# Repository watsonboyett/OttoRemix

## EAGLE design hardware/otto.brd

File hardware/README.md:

# Hardware

## Overview

Control board for servos, displays, and sensors.

## Features

### MCU
* Raytac MDBT50 module, using Nordic nRF52840 MCU
* Custom board design (very similar to Adafruit Feather nRF52840 express)

### Power
* LiPo battery input (using JST-PH header)
* Boost converter for battery to get 5V supply
* USB-C charging (rate is configurabale, default is set to 200mA)
* Power/shut-down switch, battery can be charged while ON or OFF

### Servo Motors
* 6 servo motor connections (3 on left side, 3 on right side)
* Powered from 5V supply

### LED Matrix
* P/N: Adafruit Featherwing LED Matrix
* Uses I2C bus for communication (address: 0x70)
* Powered from 5V supply
* 4-pin header

### Touch Sensor 
* P/N: Azoteq TPS43-201A-S
* Uses I2C bus for communication (address: 0x74)
* Uses GPIO input for interrupt signal from sensor
* Powered from 3.3V supply
* 5-pin header

### IMU 
* P/N: Bosch BMX160
* Uses I2C bus for communication (address: 0x68)

### Ultrasonic Range Sensor
* P/N: 
* Uses 2 GPIO pins for trig and echo signals
* Powered from 3.3V supply
* 4-pin header

### Speaker
* P/N: 
* Uses PWM output from MCU to drive audio amplifier
* RC filter on amp inputs
* Powered from 5V supply
* 2-pin header

### Buzzer
* P/N: 
* Uses PWM output from MCU
* Uses transistor to drive buzzer from 5V supply
* 2-pin header

### ON/OFF Switch
* Controls the 3.3V and 5V regulator enable circuitry 
* Not wired in-line with power supplies, so low power switched can be used
* Very low current draw when in shut-down (approx. 40 uA)
* 2 pin header

## Manufacturing Info

* outer dimensions: 56 mm x 49 mm (2.2" x 1.9")
* thickness: 1.00 mm (0.040")
* min. trace/space: 8 mil, 8 mil
* min. drill: 0.25 mm (10 mil)
* min. cutout radius: 0.4 mm (0.015")
* surface finish: ENIG
* soldermask: both sides, black
* silkscreen: both sides, white
* impedance control: none
* stackup: 4 layers

## Revision History

### v1A

* Initial design

### v2A

* Fixed schematic typo: D8 changed to D9, to reflect actual pin number
* Added 100 uF caps near servo and LED power supply pins
* Changed external board caps to 10 uF
* Removed buzzer (uses speaker only)
* Moved external connectors/silkscreen to bottom side (re-arranged all locations)
* Added power selector IC (P/N: TPS2115) for USB-VBUS vs. battery (defaults to VBUS if both present)
* Added support/connector for PIR sensor (pwr, gnd, IO/interrupt)
* Added PDM microphone (P/N: SPK0641HT4H, port on top)
* Added temp/humidity sensor (P/N: SHT41)
* Added ambient light sensor (P/N: APDS-9250) and light pipe
* Added air pressure sensor (P/N: LPS22HB)
* Added air quality/VOC sensor (P/N: SGP41)
* Added neopixel LED (SK6812-mini) and light pipe

### Future Changes

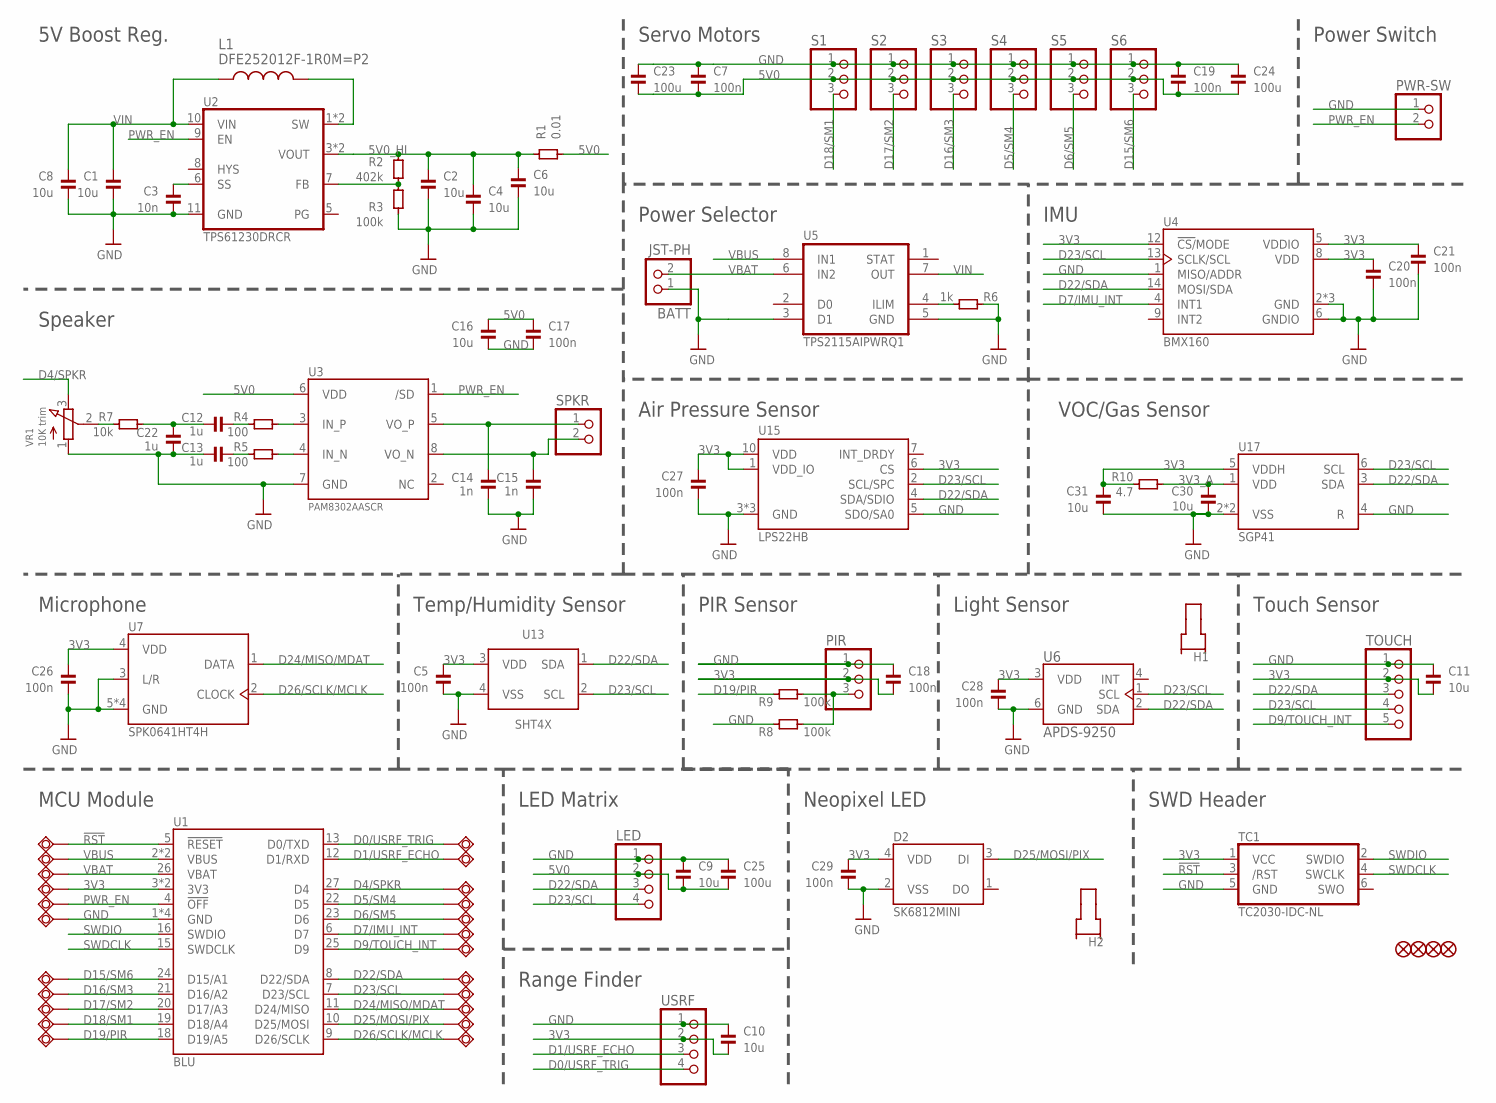
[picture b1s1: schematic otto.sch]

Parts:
3V3: TPSQTP10R; TP10R
BATT: JST-PH; JSTPH2-S2B
C1, C2, C4, C6, C8, C9, C10, C11, C16, C30, C31: 10u; _0603; MPN CL21A106KAYNNNE
C3: 10n; _0603; MPN CL21A106KAYNNNE
C5, C7, C17, C18, C19, C20, C21, C26, C27, C28, C29: 100n; _0603; MPN CL21A106KAYNNNE
C12, C13, C22: 1u; _0603; MPN CL21A106KAYNNNE
C14, C15: 1n; _0603; MPN CL21A106KAYNNNE
C23, C24, C25: 100u; _1206; MPN CL21A106KAYNNNE
D0, D1, D4, D5, D6, D7, D9, D15, D16, D17, D18, D19, D24, D25, D26: TPSQTP10R; TP10R
D2: SK6812MINI
FID1, FID2, FID3, FID5: FIDUCIAL0.8MM; FIDUCIAL_0.8MM
GND: TPSQTP10R; TP10R
H1, H2: VLP-XXX-X
L1: DFE252012F-1R0M=P2; INDC2520X120N
LED: PINHD-1X4; 1X04
PEN: TPSQTP10R; TP10R
PIR: PINHD-1X3; 1X03
PWR-SW: PINHD-1X2; 1X02
R1: 0.01; _0603
R2: 402k; _0603
R3, R8, R9: 100k; _0603
R4, R5: 100; _0603
R6: 1k; _0603
R7: 10k; _0603
R10: 4.7; _0603
RST: TPSQTP10R; TP10R
S1, S2, S3, S4, S5, S6: PINHD-1X3; 1X03
SCL: TPSQTP10R; TP10R
SDA: TPSQTP10R; TP10R
SPKR: PINHD-1X2; 1X02
TC1: TC2030-IDC-NL; TC2030-NL
TOUCH: PINHD-1X5; 1X05
U1: BLU
U2: TPS61230DRCR; VREG_V62/16624-01YE
U3: PAM8302AASCR; MSOP8_0.65MM
U4: BMX160; PQFN50P250X300X100-14N
U5: TPS2115AIPWRQ1; SOP65P640X120-8N
U6: APDS-9250; SON65P200X200X75-6N
U7: SPK0641HT4H; SPK0641HT4H-1
U13: SHT4X; SHT4X-DFN4
U15: LPS22HB; HLGA-10L
U17: SGP41
USRF: PINHD-1X4; 1X04
VBS: TPSQTP10R; TP10R
VBT: TPSQTP10R; TP10R
VR1: 10K trim; TRIMPOT_BOURNS_3303W

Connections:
3V3: 3V3.TP, C5.1, C10.2, C11.2, C18.2, C20.1, C21.1, C26.1, C27.1, C28.1, C29.1, C31.1, D2.4 (VDD), PIR.2, R10.1, TC1.1 (VCC), TOUCH.2, U1.3 (3V3), U1.28 (3V3), U4.5 (VDDIO), U4.8 (VDD), U4.12 (!CS/!MODE), U6.3 (VDD), U7.4 (VDD), U13.3 (VDD), U15.1 (VDD_IO), U15.6 (CS), U15.10 (VDD), U17.5 (VDDH), USRF.2
3V3_A: C30.1, R10.2, U17.1 (VDD)
5V0: C7.2, C9.2, C16.1, C17.1, C19.2, C23.2, C24.2, C25.2, LED.2, R1.1, S1.2, S2.2, S3.2, S4.2, S5.2, S6.2, U3.6 (VDD)
5V0_HI: C2.1, C4.1, C6.1, R1.2, R2.1, U2.3 (VOUT), U2.4 (VOUT)
!RST: RST.TP, TC1.3 (/RST), U1.5 (!RESET)
D0/USRF_TRIG: D0.TP, U1.13 (D0/TXD), USRF.4
D1/USRF_ECHO: D1.TP, U1.12 (D1/RXD), USRF.3
D4/SPKR: D4.TP, U1.27 (D4), VR1.3 (E)
D5/SM4: D5.TP, S4.3, U1.22 (D5)
D6/SM5: D6.TP, S5.3, U1.23 (D6)
D7/IMU_INT: D7.TP, U1.6 (D7), U4.4 (INT1)
D9/TOUCH_INT: D9.TP, TOUCH.5, U1.25 (D9)
D15/SM6: D15.TP, S6.3, U1.24 (D15/A1)
D16/SM3: D16.TP, S3.3, U1.21 (D16/A2)
D17/SM2: D17.TP, S2.3, U1.20 (D17/A3)
D18/SM1: D18.TP, S1.3, U1.19 (D18/A4)
D19/PIR: D19.TP, R9.1, U1.18 (D19/A5)
D22/SDA: LED.3, SDA.TP, TOUCH.3, U1.8 (D22/SDA), U4.14 (MOSI/SDA), U6.2 (SDA), U13.1 (SDA), U15.4 (SDA/SDIO), U17.3 (SDA)
D23/SCL: LED.4, SCL.TP, TOUCH.4, U1.7 (D23/SCL), U4.13 (SCLK/SCL), U6.1 (SCL), U13.2 (SCL), U15.2 (SCL/SPC), U17.6 (SCL)
D24/MISO/MDAT: D24.TP, U1.11 (D24/MISO), U7.1 (DATA)
D25/MOSI/PIX: D2.3 (DI), D25.TP, U1.10 (D25/MOSI)
D26/SCLK/MCLK: D26.TP, U1.9 (D26/SCLK), U7.2 (CLOCK)
GND: BATT.1, C1.2, C2.2, C3.2, C4.2, C5.2, C6.2, C7.1, C8.2, C9.1, C10.1, C11.1, C13.1, C14.1, C15.1, C16.2, C17.2, C18.1, C19.1, C20.2, C21.2, C22.1, C23.1, C24.1, C25.1, C26.2, C27.2, C28.2, C29.2, C30.2, C31.2, D2.2 (VSS), GND.TP, LED.1, PIR.1, PWR-SW.1, R3.2, R6.1, R8.1, S1.1, S2.1, S3.1, S4.1, S5.1, S6.1, TC1.5 (GND), TOUCH.1, U1.1 (GND), U1.14 (GND), U1.17 (GND), U1.30 (GND), U2.11 (GND), U3.7 (GND), U4.1 (MISO/ADDR), U4.2 (GND), U4.3 (GND), U4.6 (GNDIO), U4.7 (GND), U5.3 (D1), U5.5 (GND), U6.6 (GND), U7.3 (L/R), U7.5 (GND), U7.6 (GND), U7.7 (GND), U7.8 (GND), U13.4 (VSS), U15.3 (GND), U15.5 (SDO/SA0), U15.8 (GND), U15.9 (GND), U17.2 (VSS), U17.4 (R), U17.EP (VSS), USRF.1, VR1.1 (A)
unnamed: C3.1, U2.6 (SS)
unnamed: R2.2, R3.1, U2.7 (FB)
unnamed: R7.1, VR1.2 (S)
unnamed: C12.1, C22.2, R7.2
unnamed: PIR.3, R8.2, R9.2
unnamed: R6.2, U5.4 (ILIM)
unnamed: L1.2, U2.1 (SW), U2.2 (SW)
unnamed: C12.2, R4.1
unnamed: C13.2, R5.1
unnamed: R4.2, U3.3 (IN_P)
unnamed: R5.2, U3.4 (IN_N)
unnamed: C14.2, SPKR.1, U3.5 (VO_P)
unnamed: C15.2, SPKR.2, U3.8 (VO_N)
PWR_EN: PEN.TP, PWR-SW.2, U1.4 (!OFF), U2.9 (EN), U3.1 (/SD)
SWDCLK: TC1.4 (SWCLK), U1.15 (SWDCLK)
SWDIO: TC1.2 (SWDIO), U1.16 (SWDIO)
VBAT: BATT.2, U1.26 (VBAT), U5.6 (IN2), VBT.TP
VBUS: U1.2 (VBUS), U1.29 (VBUS), U5.8 (IN1), VBS.TP
VIN: C1.1, C8.1, L1.1, U2.10 (VIN), U5.7 (OUT)

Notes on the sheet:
MCU Module
5V Boost Reg.
SWD Header
Servo Motors
Power Switch
Touch Sensor
Range Finder
LED Matrix
Speaker
Microphone
IMU
Power Selector
Temp/Humidity Sensor
PIR Sensor
Light Sensor
Air Pressure Sensor
Neopixel LED
VOC/Gas Sensor

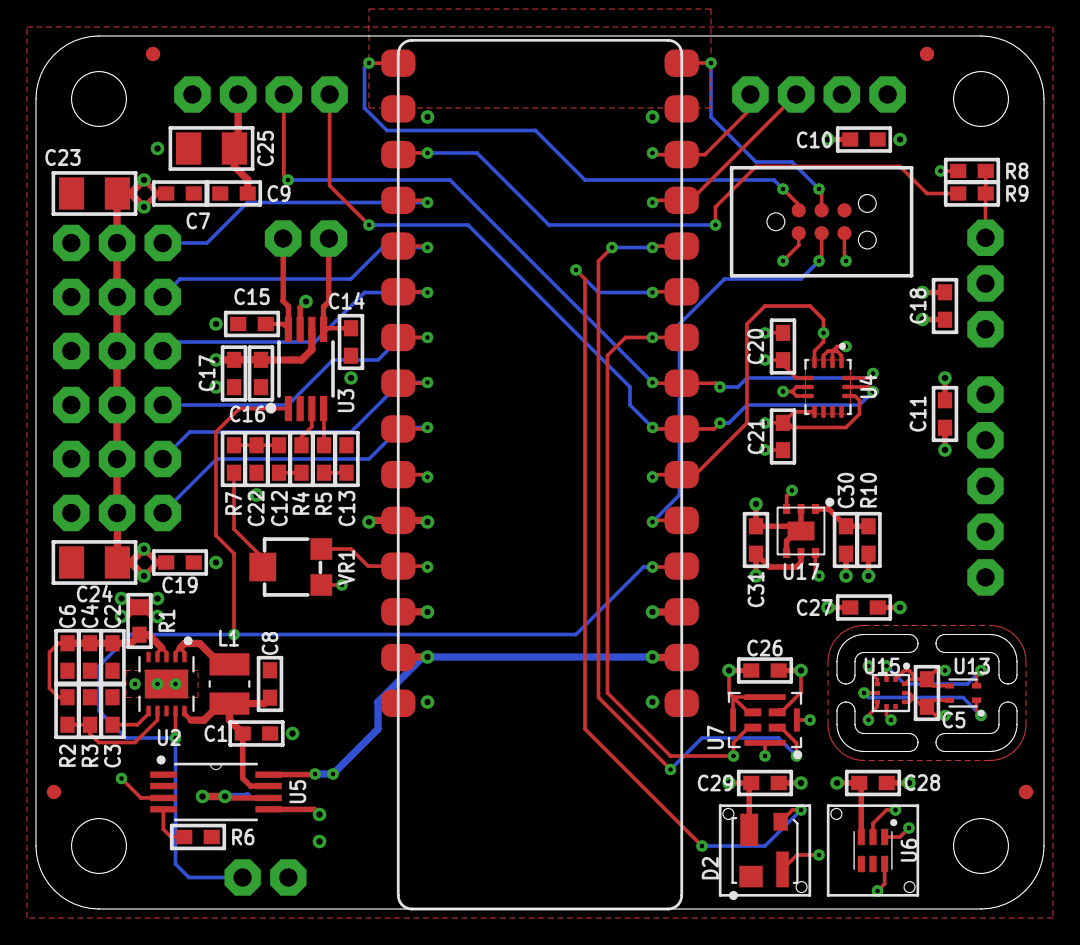
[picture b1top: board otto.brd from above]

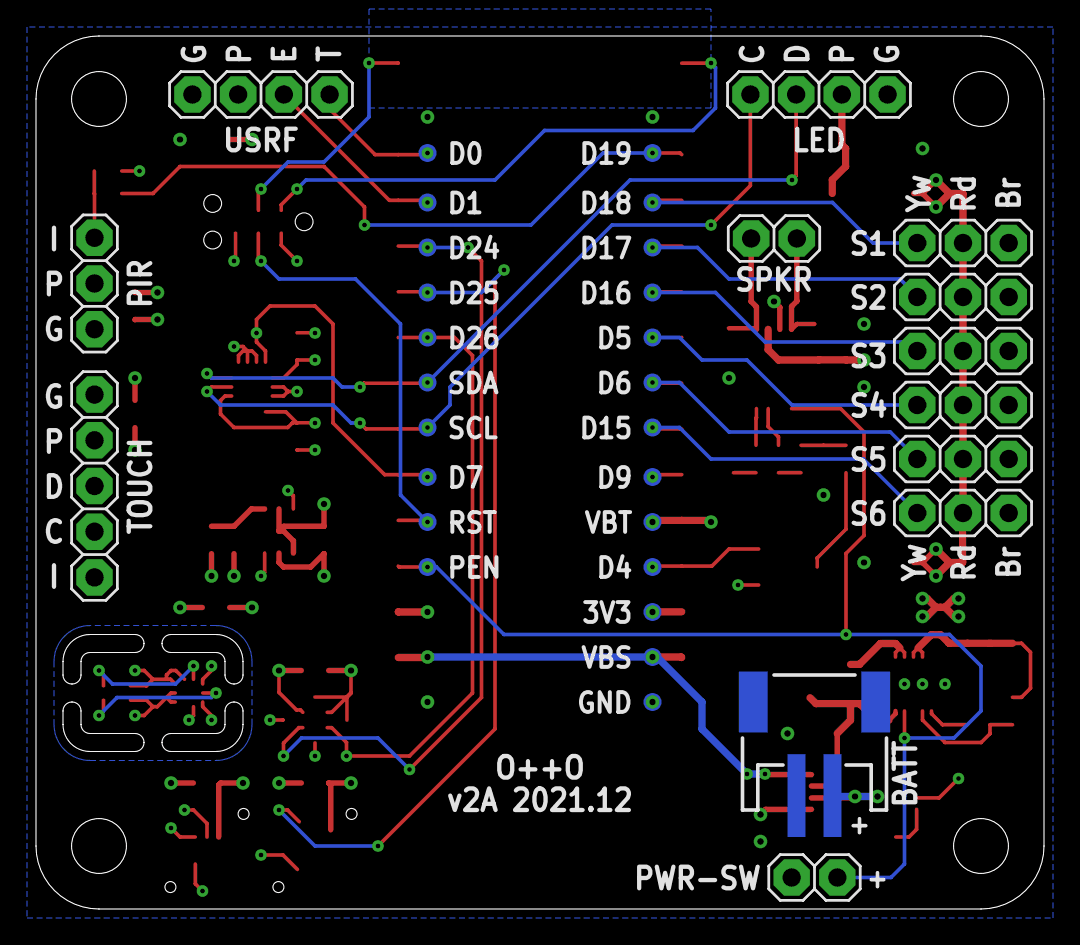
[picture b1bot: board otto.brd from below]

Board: 4 copper layers, 56.0 x 48.5 mm, 101 parts (36 on the bottom side), 42 nets.

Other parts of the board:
U$5, U$6, U$7, U$8: HOLE_4-40_NORM_BUTTON

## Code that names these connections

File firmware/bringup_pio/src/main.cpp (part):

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// IMU
// *********************************************************************

//const int IMU_INT_PIN = 0;
//const int IMU_ADDR = 0x00;
//const int IMU_BUS = 0x00;

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// Rangefinder
// *********************************************************************

const int USRF_ECHO_PIN = 18;
const int USRF_TRIG_PIN = 19;

USRF usrf = USRF(USRF_TRIG_PIN, USRF_ECHO_PIN);
timed_task_t usrf_task = {.tick_interval = 200, .tick_count = 0};

// *********************************************************************
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
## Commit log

2020-11-09 Initial hardware design
2020-11-09 Initial firmware for bringup and testing
2020-11-15 Implemented tasks using soft timer
2020-11-15 Clean up and refactoring
2021-11-24 BLE app kinda works now, but only with the servos
2021-12-22 Most features seem to work now
2021-12-22 Hardware changes for v1B, see readme file
2021-12-22 Testing for IMU calibration, SD/FAT file support, BLE support
2021-12-22 Added support for saving/loading config files on flash
2022-01-03 Lots of PCB changes v2 (see hardware readme)

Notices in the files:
hardware/otto.sch:
LICENSE: CC-BY-SA
